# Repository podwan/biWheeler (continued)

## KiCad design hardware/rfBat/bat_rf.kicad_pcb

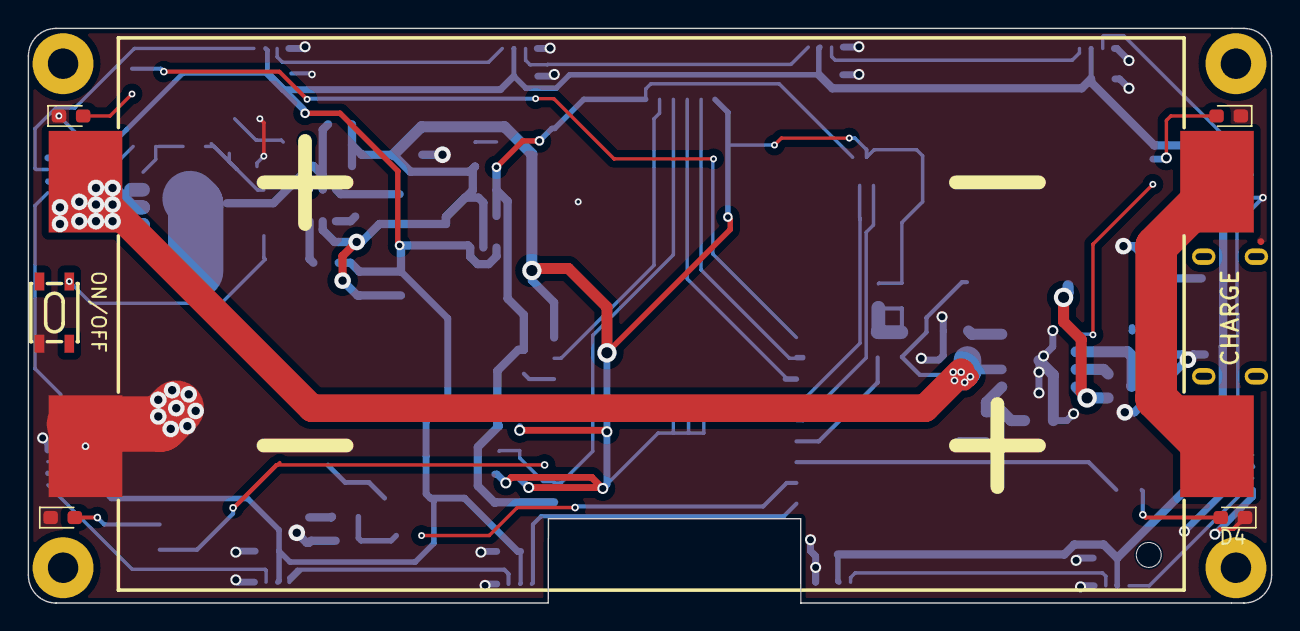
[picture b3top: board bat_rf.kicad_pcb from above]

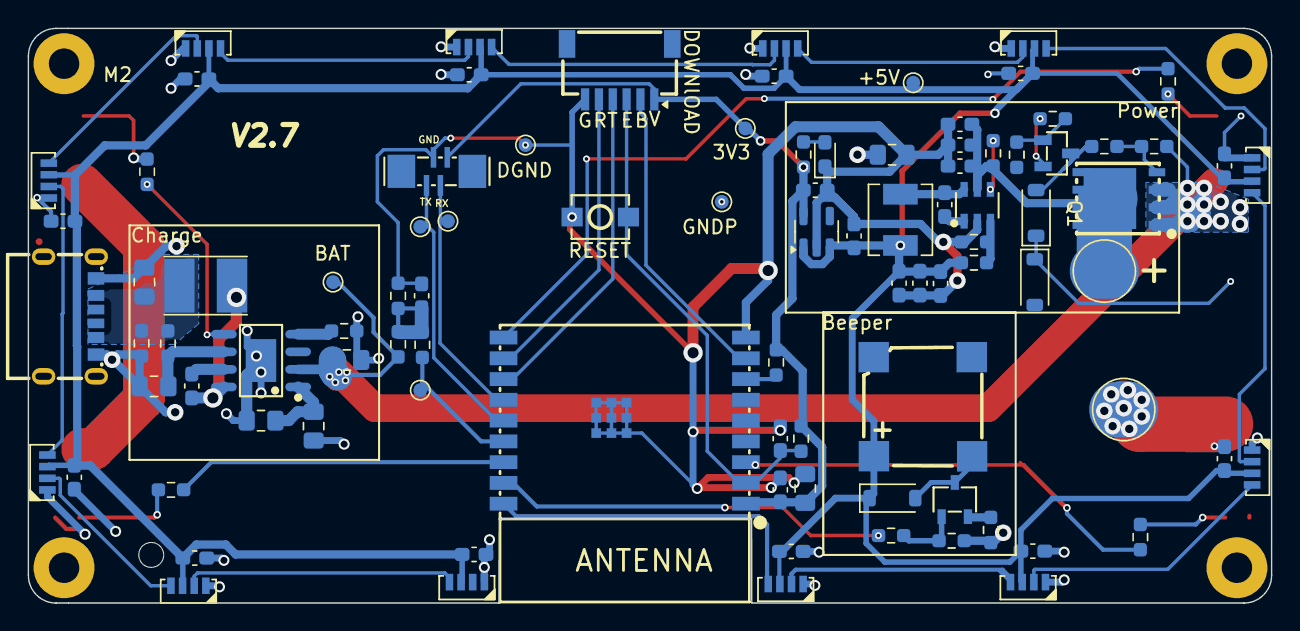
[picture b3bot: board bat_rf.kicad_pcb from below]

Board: 2 copper layers, 89.8 x 41.5 mm, 105 parts (95 on the bottom side), 57 nets.

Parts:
BT1: doubleBatCell; BAT-SMD_BH-18650-B1BA007
C1, C4: 2.2u; C_0603_1608Metric_Pad1.08x0.95mm_HandSolder
C2, C5, C6, C7, C11, C13, C14, C16, C17, C18, C27, C30, C31, C32, C33, C34, C35, C36, C37: 100n; C_0603_1608Metric_Pad1.08x0.95mm_HandSolder
C3, C8: 10u; C_0603_1608Metric_Pad1.08x0.95mm_HandSolder
C9, C15: 1u; C_0603_1608Metric_Pad1.08x0.95mm_HandSolder
C10, C26: 22u; C_0805_2012Metric_Pad1.18x1.45mm_HandSolder
C12, C28, C29, C40: 10u; C_0805_2012Metric_Pad1.18x1.45mm_HandSolder
D1, D5, D7: 1N4148W; D_SOD-123
D2: RED; LED_0603_1608Metric_Pad1.05x0.95mm_HandSolder
D3: G_LED; LED_0603_1608Metric_Pad1.05x0.95mm_HandSolder
D4: Y_LED; LED_0603_1608Metric_Pad1.05x0.95mm_HandSolder
D6: LED; LED_0603_1608Metric_Pad1.05x0.95mm_HandSolder
D13: B_LED; LED_0603_1608Metric_Pad1.05x0.95mm_HandSolder
FB1: FerriteBead_Small; C_0805_2012Metric_Pad1.18x1.45mm_HandSolder
H1, H2, H3, H4: MountingHole; MountingHole_2.2mm_M2_Pad
J1: USB_C_Receptacle_PowerOnly_6P; USB-C-SMD_HX-TYPE-C-6PIN
J2, J5: Conn_01x01_Pin; TestPoint_Pad_D4.0mm
J3: Conn_01x06; CONN-SMD_6P-P1.00_XYECONN_XY-SH1.0-6A61
L1: 10uH; L_Chilisin_BMRA00040420
L2: 2.2uH; L_Taiyo-Yuden_NR-40xx_HandSoldering
LED1, LED2, LED3, LED4, LED5, LED6, LED7, LED8, LED9, LED10, LED11, LED12: XL-4020RGBC-WS2812B; LED-SMD_4P-L4.0-W1.7_M4020-03003-RGB-862-001
P1: FPC_0.5MM_4P_Vertical_mounting_type_H2.0mm; FPC-SMD_4P-L7.5-W2.0-P0.50
Q1: IRFH7440TRPBF; DFN-8_L5.8-W4.9-P1.27-LS6.0-BL-1
Q5: AllPower__AP2300; SOT-23
R1: 0.5R; R_0603_1608Metric_Pad0.98x0.95mm_HandSolder
R2: 5k1; R_0603_1608Metric_Pad0.98x0.95mm_HandSolder
R3, R5, R13, R15: 3k; R_0603_1608Metric_Pad0.98x0.95mm_HandSolder
R4, R7, R8, R12, R21: 10k; R_0603_1608Metric_Pad0.98x0.95mm_HandSolder
R6, R19: 100R; R_0603_1608Metric_Pad0.98x0.95mm_HandSolder
R9: 7.5m; R_0603_1608Metric_Pad0.98x0.95mm_HandSolder
R10: 3m; R_0603_1608Metric_Pad0.98x0.95mm_HandSolder
R11: 22k; R_0603_1608Metric_Pad0.98x0.95mm_HandSolder
R14, R16, R20: 1k; R_0603_1608Metric_Pad0.98x0.95mm_HandSolder
R17: 500R; R_0603_1608Metric_Pad0.98x0.95mm_HandSolder
R18: 51k; R_0603_1608Metric_Pad0.98x0.95mm_HandSolder
R22: 160k; R_0603_1608Metric_Pad0.98x0.95mm_HandSolder
R23: 100k; R_0603_1608Metric_Pad0.98x0.95mm_HandSolder
SW1: 3*4*2.5MM_贴片4脚; SW-SMD_4P-L4.2-W3.3-P2.15-LS5.1
SW3: TS-1199A-B-B; SW-SMD_L4.0-W2.9-LS5.0
TP1, TP2, TP3, TP4, TP5, TP7, TP9, TP11: TestPoint; TestPoint_Pad_D1.0mm
U1: ESP32-C3-WROOM-02-N4; BULETM-SMD_18P-L20.0-W18.0-P1.50_ESP32-C3-WROOM
U2: IP2325_5M_WHJC; ESOP-8_L4.9-W3.9-P1.27-LS6.0-BL-EP3.1
U3: MT2492; SOT-23-6_L2.9-W1.6-P0.95-LS2.8-BL
U4: SS8050_C7420370; SOT-23-3_L2.9-W1.3-P1.90-LS2.4-BR
U5: MLT-8530-5V; BUZ-SMD_4P-L8.5-W8.5-TL
U7: XC6220B331MR; SOT-23-5

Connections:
+3V3: C12.1, C13.1, C15.1, J3.1, P1.4, R4.2, R12.2, R16.1, TP2.1, U1.1 (3V3), U7.5 (VOUT)
+5V: C4.1, C5.2, C6.2, C7.1, C8.1, C9.1, C11.2, C14.2, C17.2, C30.2, C31.2, C32.2, C33.2, C34.2, C35.2, C36.2, D5.1 (K), L1.2, LED1.3 (VDD), LED2.3 (VDD), LED3.3 (VDD), LED4.3 (VDD), LED5.3 (VDD), LED6.3 (VDD), LED7.3 (VDD), LED8.3 (VDD), LED9.3 (VDD), LED10.3 (VDD), LED11.3 (VDD), LED12.3 (VDD), R22.2, TP7.1, U5.1 (+), U7.1 (VIN), U7.3 (CE)
+BATT: BT1.1 (+), C40.1, Q1.1 (S), Q1.2 (S), Q1.3 (S), R8.2, R9.2, TP11.1, U2.2 (VOUT)
/BAT_FB: R14.1, TP5.1, U1.15 (IO3)
/BEEP: R6.1, U1.17 (IO1)
/BLUE: R13.1, U1.10 (IO10)
/EN: C16.1, J3.3, R12.1, SW3.2, U1.2 (EN)
/ESP_RX: P1.3, TP3.1, U1.13 (IO18)
/ESP_TX: P1.1, TP4.1, U1.14 (IO19)
/GREEN: R5.1, U1.3 (IO4)
/IO9: J3.2, U1.8 (IO9)
/K1: D7.2 (A), R19.1, U4.3 (C)
/KEY: D1.2 (A), U1.6 (IO7)
/POWER_EN: R20.1, U1.5 (IO6)
/RGB: LED7.4 (DI), U1.18 (IO0)
/RXD: J3.5, U1.11 (RXD)
/TXD: J3.4, U1.12 (TXD)
/YELLOW: R15.1, U1.16 (IO2)
GNDD: C1.2, C2.2, C3.2, C4.2, C7.2, C8.2, C9.2, C12.2, C13.2, C15.2, C16.2, C37.2, D6.1 (K), FB1.2, J3.6, P1.2, R10.1, R11.2, SW3.1, TP1.1, U1.9 (GND), U1.19 (EP), U3.2 (GND), U7.2 (GND)
GNDPWR: BT1.4 (-), C5.1, C6.1, C10.2, C11.1, C14.1, C17.1, C26.2, C28.2, C29.2, C30.1, C31.1, C32.1, C33.1, C34.1, C35.1, C36.1, C40.2, D2.1 (K), D3.1 (K), D4.1 (K), D13.1 (K), FB1.1, J1.A12 (GND), J1.B12 (GND), J5.1, LED1.1 (VSS), LED2.1 (VSS), LED3.1 (VSS), LED4.1 (VSS), LED5.1 (VSS), LED6.1 (VSS), LED7.1 (VSS), LED8.1 (VSS), LED9.1 (VSS), LED10.1 (VSS), LED11.1 (VSS), LED12.1 (VSS), R2.1, R7.1, R17.1, R18.1, R21.2, SW1.4, TP9.1, U2.9 (GND), U4.2 (E)
unnamed: BT1.2 (-), BT1.3 (+)
unnamed: C28.1, J1.A9 (VBUS), J1.B9 (VBUS), L2.1, R1.1, R2.2
unnamed: C37.1, R9.1, R10.2, R14.2
unnamed: D1.1 (K), D7.1 (K), SW1.1
unnamed: D2.2 (A), R3.1
unnamed: D3.2 (A), R5.2
unnamed: D4.2 (A), R15.2
unnamed: D5.2 (A), Q5.3 (D), U5.2 (-)
unnamed: D6.2 (A), R16.2
unnamed: D13.2 (A), R13.2
unnamed: LED1.4 (DI), LED2.2 (DO)
unnamed: LED1.2 (DO), LED10.4 (DI)
unnamed: LED2.4 (DI), LED3.2 (DO)
unnamed: LED3.4 (DI), LED4.2 (DO)
unnamed: LED4.4 (DI), LED5.2 (DO)
unnamed: LED5.4 (DI), LED6.2 (DO)
unnamed: LED6.4 (DI), LED7.2 (DO)
unnamed: LED8.4 (DI), LED9.2 (DO)
unnamed: LED9.4 (DI), LED10.2 (DO)
unnamed: LED11.4 (DI), LED12.2 (DO)
unnamed: LED8.2 (DO), LED12.4 (DI)
unnamed: Q1.4 (G), R8.1, R19.2
unnamed: Q5.1 (G), R6.2, R7.2
unnamed: Q5.2 (S), R17.2
unnamed: R4.1, U1.7 (IO8)
unnamed: C27.1, U2.7 (BST)
unnamed: R3.2, U2.5 (LED)
unnamed: C27.2, L2.2, U2.8 (LX)
unnamed: R18.2, U2.4 (NTC)
unnamed: C29.1, R1.2, U2.6 (VIN)
unnamed: C10.1, C26.1, U2.1 (VSYS)
unnamed: C18.1, U3.1 (BS)
unnamed: R23.1, U3.4 (EN)
unnamed: R11.1, R22.1, U3.3 (FB)
unnamed: C18.2, L1.1, U3.6 (SW)
unnamed: R20.2, R21.1, U4.1 (B)
VCC: C1.1, C2.1, C3.1, J2.1, Q1.5 (D), Q1.6 (D), Q1.7 (D), Q1.8 (D), Q1.9 (D), R23.2, U3.5 (IN)

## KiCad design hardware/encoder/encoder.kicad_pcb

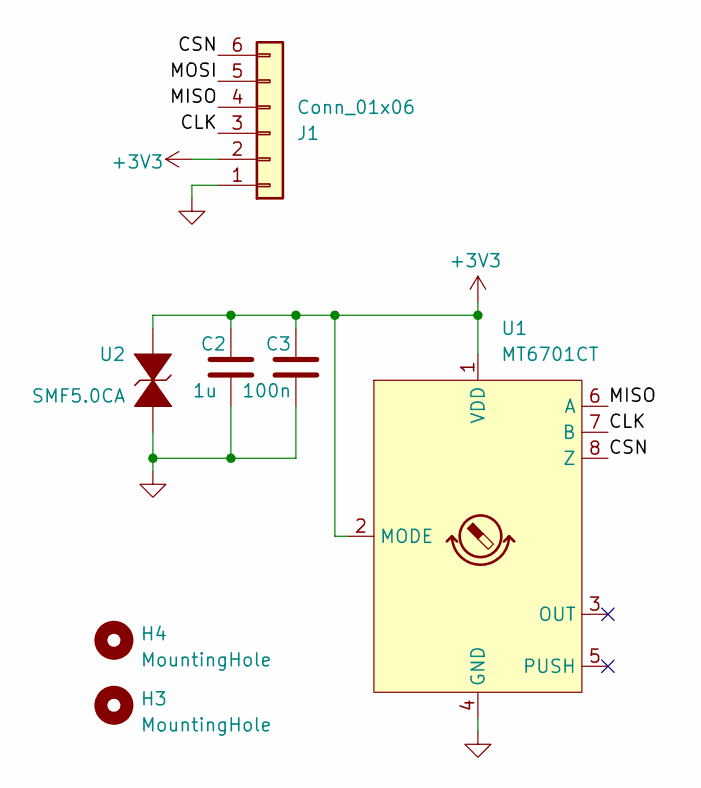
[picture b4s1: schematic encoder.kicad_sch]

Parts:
C2: 1u; C_0603_1608Metric_Pad1.08x0.95mm_HandSolder
C3: 100n; C_0603_1608Metric_Pad1.08x0.95mm_HandSolder
H3, H4: MountingHole; MountingHole_2.2mm_M2_Pad_Via
J1: Conn_01x06; FPC-SMD_6P-P0.50_HDGC_0.5K-A-6PB
U1: MT6701CT; SO-8_3.9x4.9mm_P1.27mm
U2: SMF5.0CA

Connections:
+3V3: C2.1, C3.1, J1.2, U1.1 (VDD), U1.2 (MODE), U2.1
/CLK: J1.3, U1.7 (B)
/CSN: J1.6, U1.8 (Z)
/MISO: J1.4, U1.6 (A)
/MOSI: J1.5
GND: C2.2, C3.2, J1.1, U1.4 (GND), U2.2

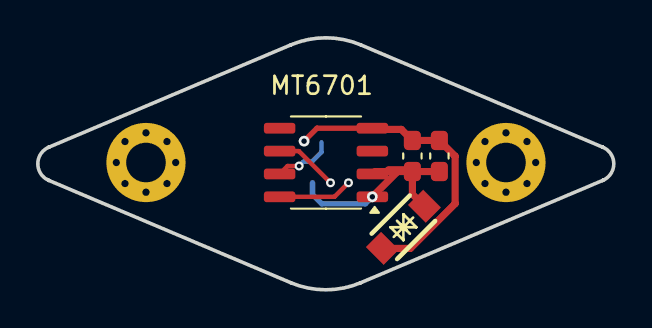
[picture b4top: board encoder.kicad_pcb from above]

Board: 2 copper layers, 32.0 x 14.0 mm, 7 parts (1 on the bottom side), 5 nets.

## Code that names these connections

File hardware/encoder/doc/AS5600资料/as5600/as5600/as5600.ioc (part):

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Mcu.Name=STM32F030F4Px
Mcu.Package=TSSOP20
Mcu.UserName=STM32F030F4Px
PA10.GPIOParameters=GPIO_Label
PA10.GPIO_Label=IIC_SDA
PA10.Signal=GPIO_Output
PA13.Mode=Serial_Wire
PA13.Signal=SYS_SWDIO
PA14.Mode=Serial_Wire
PA14.Signal=SYS_SWCLK
PA2.Mode=Asynchronous
PA2.Signal=USART1_TX
PA3.Mode=Asynchronous
PA3.Signal=USART1_RX
PA9.GPIOParameters=GPIO_Label
PA9.GPIO_Label=IIC_SCL
PA9.Signal=GPIO_Output
PF0-OSC_IN.Mode=HSE-External-Oscillator
PF0-OSC_IN.Signal=RCC_OSC_IN
PF1-OSC_OUT.Mode=HSE-External-Oscillator
PF1-OSC_OUT.Signal=RCC_OSC_OUT
RCC.SYSCLKFreq_VALUE=48000000
RCC.SYSCLKSource=RCC_SYSCLKSOURCE_PLLCLK
board=custom

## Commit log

2024-07-28 update hardware sch
